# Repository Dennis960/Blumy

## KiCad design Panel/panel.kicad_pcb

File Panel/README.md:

# Blumy Panel

To create the panel, open the root of this repository in the panel devcontainer.

Then: from the root run `python3 Panel/panel.py`.

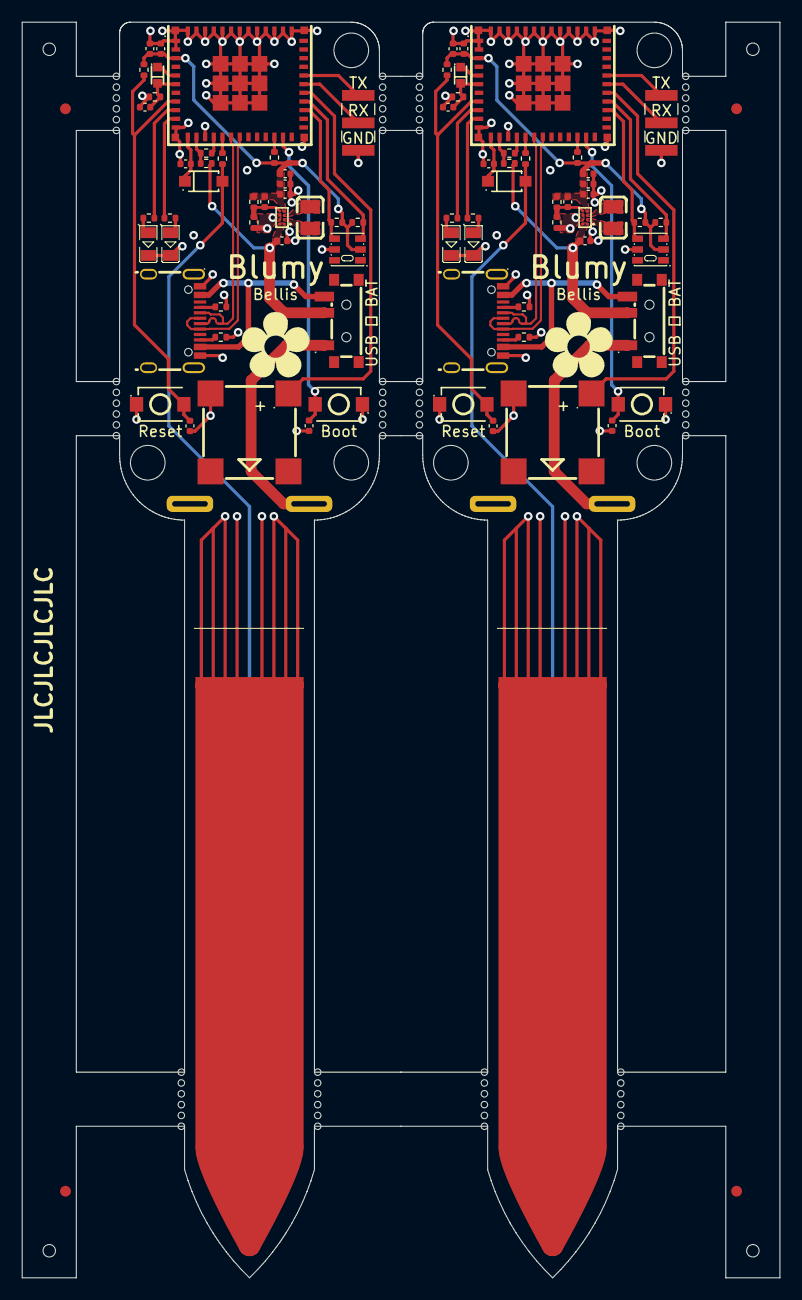
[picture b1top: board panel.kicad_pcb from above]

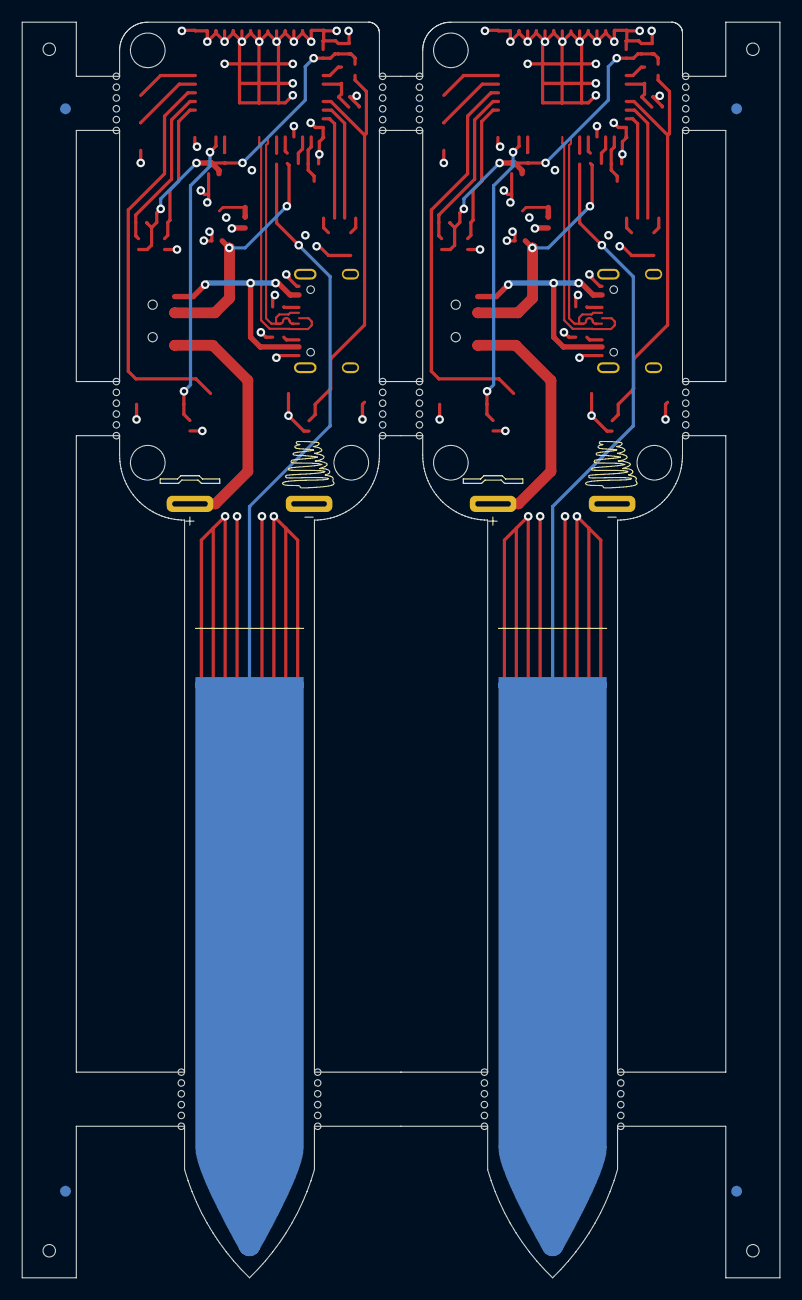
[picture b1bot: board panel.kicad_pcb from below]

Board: 4 copper layers, 70.0 x 116.0 mm, 174 parts (8 on the bottom side), 62 nets.

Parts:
BZ1, BZ1#2: Buzzer; BUZ-SMD_4P-L8.5-W8.5-P8.50-BR
C1, C1#2, C6, C6#2, C7, C7#2, C9, C9#2, C10, C10#2, C12, C12#2: 10uF; C_0402_1005Metric
C2, C2#2: 10pF; C_0402_1005Metric
C3, C3#2, C8, C8#2: 10nF; C_0402_1005Metric
C4, C4#2: 7pF-27pF, A=2.75cm^2; Sensor-Tip
C5, C5#2, C11, C11#2: 100nF-Ceramic; C_0402_1005Metric
D1, D1#2: GREEN; LED0805-R-RD
D2, D2#2: Switching-Diode; SOD-123F_L2.7-W1.6-LS3.8-RD
D3, D3#2: RED; LED0805-R-RD
Flower1, Flower1#2: Flower
H1, H1#2, H2, H2#2, H3, H3#2: MountingHole; MountingHole_3.2mm_M3
J1, J1#2: Conn_01x03; PinHeader_1x03_P2.54mm_Vertical_SMD
KiKit_FID_B_1, KiKit_FID_B_2, KiKit_FID_B_3, KiKit_FID_B_4: Fiducial
KiKit_FID_T_1, KiKit_FID_T_2, KiKit_FID_T_3, KiKit_FID_T_4: Fiducial
KiKit_MB_1_1, KiKit_MB_1_2, KiKit_MB_1_3, KiKit_MB_1_4, KiKit_MB_1_5, KiKit_MB_1_6, KiKit_MB_2_1, KiKit_MB_2_2, KiKit_MB_2_3, KiKit_MB_2_4, KiKit_MB_2_5, KiKit_MB_2_6, KiKit_MB_3_1, KiKit_MB_3_2, KiKit_MB_3_3, KiKit_MB_3_4, KiKit_MB_3_5, KiKit_MB_3_6, KiKit_MB_4_1, KiKit_MB_4_2, KiKit_MB_4_3, KiKit_MB_4_4, KiKit_MB_4_5, KiKit_MB_4_6, KiKit_MB_5_1, KiKit_MB_5_2, KiKit_MB_5_3, KiKit_MB_5_4, KiKit_MB_5_5, KiKit_MB_5_6, KiKit_MB_6_1, KiKit_MB_6_2, KiKit_MB_6_3, KiKit_MB_6_4, KiKit_MB_6_5, KiKit_MB_6_6, KiKit_MB_7_1, KiKit_MB_7_2, KiKit_MB_7_3, KiKit_MB_7_4, KiKit_MB_7_5, KiKit_MB_7_6, KiKit_MB_8_1, KiKit_MB_8_2, KiKit_MB_8_3, KiKit_MB_8_4, KiKit_MB_8_5, KiKit_MB_8_6, KiKit_MB_9_1, KiKit_MB_9_2, KiKit_MB_9_3, KiKit_MB_9_4, KiKit_MB_9_5, KiKit_MB_9_6, KiKit_MB_10_1, KiKit_MB_10_2, KiKit_MB_10_3, KiKit_MB_10_4, KiKit_MB_10_5, KiKit_MB_10_6, KiKit_MB_11_1, KiKit_MB_11_2, KiKit_MB_11_3, KiKit_MB_11_4, KiKit_MB_11_5, KiKit_MB_11_6, KiKit_MB_12_1, KiKit_MB_12_2, KiKit_MB_12_3, KiKit_MB_12_4, KiKit_MB_12_5, KiKit_MB_12_6: NPTH
KiKit_TO_1, KiKit_TO_2, KiKit_TO_3, KiKit_TO_4: NPTH
L1, L1#2: 1.5uH; L0806
R1, R1#2: 287k; R_0402_1005Metric
R2, R2#2, R4, R4#2, R10, R10#2, R11, R11#2, R12, R12#2: 5k1; R_0402_1005Metric
R3, R3#2: 100k; R_0402_1005Metric
R5, R5#2, R8, R8#2, R9, R9#2: 10k; R_0402_1005Metric
R6, R6#2: 2k; R_0402_1005Metric
R13, R13#2, R14, R14#2: 120; R_0402_1005Metric
R15, R15#2: 51.1k; R_0402_1005Metric
REF1, REF1#2: TPS63036YFGR; DSBGA-8_L1.8-W1.1-R2-C4-P0.40-BR
U1, U1#2: USB-C; USB-C-SMD_G-SWITCH_GT-USB-7010EN
U3, U3#2: AHT20; SENSOR-SMD-6_AHT20
U4, U4#2, U7, U7#2: Tactile-Switch; SW-SMD_L3.9-W3.0-P4.45
U6, U6#2: Light sensor; SENSORS-SMD_ALS-PT19
U8, U8#2: Slide-Switch; SW-SMD_MK-12C02-G025
U9, U9#2: Battery-Spring; AAA Battery-spring
U13, U13#2: ESP32-C6-MINI-1-N4; WIFIM-SMD_61P-L16.6-W13.2-P0.80-ESP32-C6-MINI-1-N4

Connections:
Board_0-+3V3: C2#2.1, C6#2.1, C8#2.1, C9.1, C10#2.1, C12.1, R1#2.1, R2.2, R5.2, R9#2.1, R10.2, REF1#2.D1 (VOUT), U3#2.2 (VDD), U13.3 (3V3)
Board_0-ADC_Light_Sensor: C7#2.1, R3#2.1, U6#2.2 (E), U13.6 (IO3)
Board_0-ADC_Moisture: C3.2, D2.1 (K), U13.12 (IO0)
Board_0-ADC_Voltage_Measurement: R4#2.2, R6#2.1, U13.13 (IO1)
Board_0-Buzzer: BZ1.1 (+), U13.29 (IO23)
Board_0-EN: C11#2.1, R9#2.2, U4#2.2, U13.8 (EN)
Board_0-GND: BZ1.2, C1.2, C3.1, C4.2, C5.2, C6#2.2, C7#2.2, C8#2.2, C9.2, C10#2.2, C11#2.2, C12.2, D1.2 (K), D3.2 (-), J1#2.3, R3#2.2, R11#2.1, R12.1, R15#2.2, REF1#2.B2 (PS/SYNC), REF1#2.C2 (GND), U1.A1B12 (GND), U1.B1A12 (GND), U3#2.5 (GND), U4#2.1, U7#2.1, U9.2 (-), U13.1 (GND), U13.2 (GND), U13.11 (GND), U13.14 (GND), U13.36 (GND), U13.37 (GND), U13.38 (GND), U13.39 (GND), U13.40 (GND), U13.41 (GND), U13.42 (GND), U13.43 (GND), U13.44 (GND), U13.45 (GND), U13.46 (GND), U13.47 (GND), U13.48 (GND), U13.49 (GND), U13.50 (GND), U13.51 (GND), U13.52 (GND), U13.53 (GND)
Board_0-IO8: R5.1, U13.22 (IO8)
Board_0-IO9: C5.1, U7#2.2, U13.23 (IO9)
Board_0-LED_Green: R13.1, U13.10 (IO5)
Board_0-LED_Red: R14#2.1, U13.9 (IO4)
Board_0-Light_Sensor_In: U6#2.1 (C), U13.5 (IO2)
Board_0-Moisture_SensorCapV: C4.1, D2.2 (A), R8.1
Board_0-Moisture_Square_Wave_Signal: R8.2, U13.16 (IO7)
Board_0-Net-(D1-A): D1.1 (A), R13.2
Board_0-Net-(D3-+): D3.1 (+), R14#2.2
Board_0-Net-(REF1-L1): L1.2, REF1#2.B1 (L1)
Board_0-Net-(REF1-L2): L1.1, REF1#2.C1 (L2)
Board_0-PWR_BAT_VIN: U8.1, U9.1 (+)
Board_0-PWR_FB: C2#2.2, R1#2.2, R15#2.1, REF1#2.D2 (FB)
Board_0-PWR_USB_CC1: R11#2.2, U1.A5 (CC1)
Board_0-PWR_USB_CC2: R12.2, U1.B5 (CC2)
Board_0-PWR_USB_VIN: U1.A4B9 (VBUS), U1.B4A9 (VBUS), U8.3
Board_0-PWR_VIN: C1.1, R4#2.1, REF1#2.A1 (VIN), REF1#2.A2 (EN), U8.2
Board_0-RX: J1#2.2, U13.30 (RXD0)
Board_0-TH_SCL: R2.1, U3#2.3 (SCL), U13.28 (IO22)
Board_0-TH_SDA: R10.1, U3#2.4 (SDA), U13.27 (IO21)
Board_0-TX: J1#2.1, U13.31 (TXD0)
Board_0-USB_D+: U1.A6 (D+), U1.B6 (D+), U13.18 (IO13)
Board_0-USB_D-: U1.A7 (D-), U1.B7 (D-), U13.17 (IO12)
Board_0-Voltage_Measurement_Select: R6#2.2, U13.15 (IO6)
Board_1-+3V3: C2.1, C6.1, C8.1, C9#2.1, C10.1, C12#2.1, R1.1, R2#2.2, R5#2.2, R9.1, R10#2.2, REF1.D1 (VOUT), U3.2 (VDD), U13#2.3 (3V3)
Board_1-ADC_Light_Sensor: C7.1, R3.1, U6.2 (E), U13#2.6 (IO3)
Board_1-ADC_Moisture: C3#2.2, D2#2.1 (K), U13#2.12 (IO0)
Board_1-ADC_Voltage_Measurement: R4.2, R6.1, U13#2.13 (IO1)
Board_1-Buzzer: BZ1#2.1 (+), U13#2.29 (IO23)
Board_1-EN: C11.1, R9.2, U4.2, U13#2.8 (EN)
Board_1-GND: BZ1#2.2, C1#2.2, C3#2.1, C4#2.2, C5#2.2, C6.2, C7.2, C8.2, C9#2.2, C10.2, C11.2, C12#2.2, D1#2.2 (K), D3#2.2 (-), J1.3, R3.2, R11.1, R12#2.1, R15.2, REF1.B2 (PS/SYNC), REF1.C2 (GND), U1#2.A1B12 (GND), U1#2.B1A12 (GND), U3.5 (GND), U4.1, U7.1, U9#2.2 (-), U13#2.1 (GND), U13#2.2 (GND), U13#2.11 (GND), U13#2.14 (GND), U13#2.36 (GND), U13#2.37 (GND), U13#2.38 (GND), U13#2.39 (GND), U13#2.40 (GND), U13#2.41 (GND), U13#2.42 (GND), U13#2.43 (GND), U13#2.44 (GND), U13#2.45 (GND), U13#2.46 (GND), U13#2.47 (GND), U13#2.48 (GND), U13#2.49 (GND), U13#2.50 (GND), U13#2.51 (GND), U13#2.52 (GND), U13#2.53 (GND)
Board_1-IO8: R5#2.1, U13#2.22 (IO8)
Board_1-IO9: C5#2.1, U7.2, U13#2.23 (IO9)
Board_1-LED_Green: R13#2.1, U13#2.10 (IO5)
Board_1-LED_Red: R14.1, U13#2.9 (IO4)
Board_1-Light_Sensor_In: U6.1 (C), U13#2.5 (IO2)
Board_1-Moisture_SensorCapV: C4#2.1, D2#2.2 (A), R8#2.1
Board_1-Moisture_Square_Wave_Signal: R8#2.2, U13#2.16 (IO7)
Board_1-Net-(D1-A): D1#2.1 (A), R13#2.2
Board_1-Net-(D3-+): D3#2.1 (+), R14.2
Board_1-Net-(REF1-L1): L1#2.2, REF1.B1 (L1)
Board_1-Net-(REF1-L2): L1#2.1, REF1.C1 (L2)
Board_1-PWR_BAT_VIN: U8#2.1, U9#2.1 (+)
Board_1-PWR_FB: C2.2, R1.2, R15.1, REF1.D2 (FB)
Board_1-PWR_USB_CC1: R11.2, U1#2.A5 (CC1)
Board_1-PWR_USB_CC2: R12#2.2, U1#2.B5 (CC2)
Board_1-PWR_USB_VIN: U1#2.A4B9 (VBUS), U1#2.B4A9 (VBUS), U8#2.3
Board_1-PWR_VIN: C1#2.1, R4.1, REF1.A1 (VIN), REF1.A2 (EN), U8#2.2
Board_1-RX: J1.2, U13#2.30 (RXD0)
Board_1-TH_SCL: R2#2.1, U3.3 (SCL), U13#2.28 (IO22)
Board_1-TH_SDA: R10#2.1, U3.4 (SDA), U13#2.27 (IO21)
Board_1-TX: J1.1, U13#2.31 (TXD0)
Board_1-USB_D+: U1#2.A6 (D+), U1#2.B6 (D+), U13#2.18 (IO13)
Board_1-USB_D-: U1#2.A7 (D-), U1#2.B7 (D-), U13#2.17 (IO12)
Board_1-Voltage_Measurement_Select: R6.2, U13#2.15 (IO6)

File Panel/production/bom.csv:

Designator,Footprint,Quantity,Value,LCSC Part #
"BZ1_2, BZ1",BUZ-SMD_4P-L8.5-W8.5-P8.50-BR,2,Buzzer,C94599
"C1_2, C1, C10_2, C10, C12_2, C12, C6_2, C6, C7_2, C7, C9_2, C9",0402,12,10uF,C15525
"C11_2, C11, C5_2, C5",0402,4,100nF-Ceramic,C1525
"C2_2, C2",0402,2,10pF,C32949
"C3_2, C3, C8_2, C8",0402,4,10nF,C15195
"D1_2, D1",LED0805-R-RD,2,GREEN,C2297
"D2_2, D2",SOD-123F_L2.7-W1.6-LS3.8-RD,2,Switching-Diode,C81598
"D3_2, D3",LED0805-R-RD,2,RED,C84256
"L1_2, L1",L0806,2,1.5uH,C668311
"R1_2, R1",0402,2,287k,C321426
"R10_2, R10, R11_2, R11, R12_2, R12, R2_2, R2, R4_2, R4",0402,10,5k1,C25905
"R13_2, R13, R14_2, R14",0402,4,120,C25079
"R15_2, R15",0402,2,51.1k,C284602
"R3_2, R3",0402,2,100k,C25741
"R5_2, R5, R8_2, R8, R9_2, R9",0402,6,10k,C25744
"R6_2, R6",0402,2,2k,C4109
"REF1_2, REF1",DSBGA-8_L1.8-W1.1-R2-C4-P0.40-BR,2,TPS63036YFGR,C283955
"U1_2, U1",USB-C-SMD_G-SWITCH_GT-USB-7010EN,2,USB-C,C2997435
"U13_2, U13",WIFIM-SMD_61P-L16.6-W13.2-P0.80-ESP32-C6-MINI-1-N4,2,ESP32-C6-MINI-1-N4,C5736265
"U3_2, U3",SENSOR-SMD-6_AHT20,2,AHT20,C2757850
"U4_2, U4, U7_2, U7",SW-SMD_L3.9-W3.0-P4.45,4,Tactile-Switch,C720477
"U6_2, U6",SENSORS-SMD_ALS-PT19,2,Light sensor,C146233
"U8_2, U8",SW-SMD_MK-12C02-G025,2,Slide-Switch,C778186
